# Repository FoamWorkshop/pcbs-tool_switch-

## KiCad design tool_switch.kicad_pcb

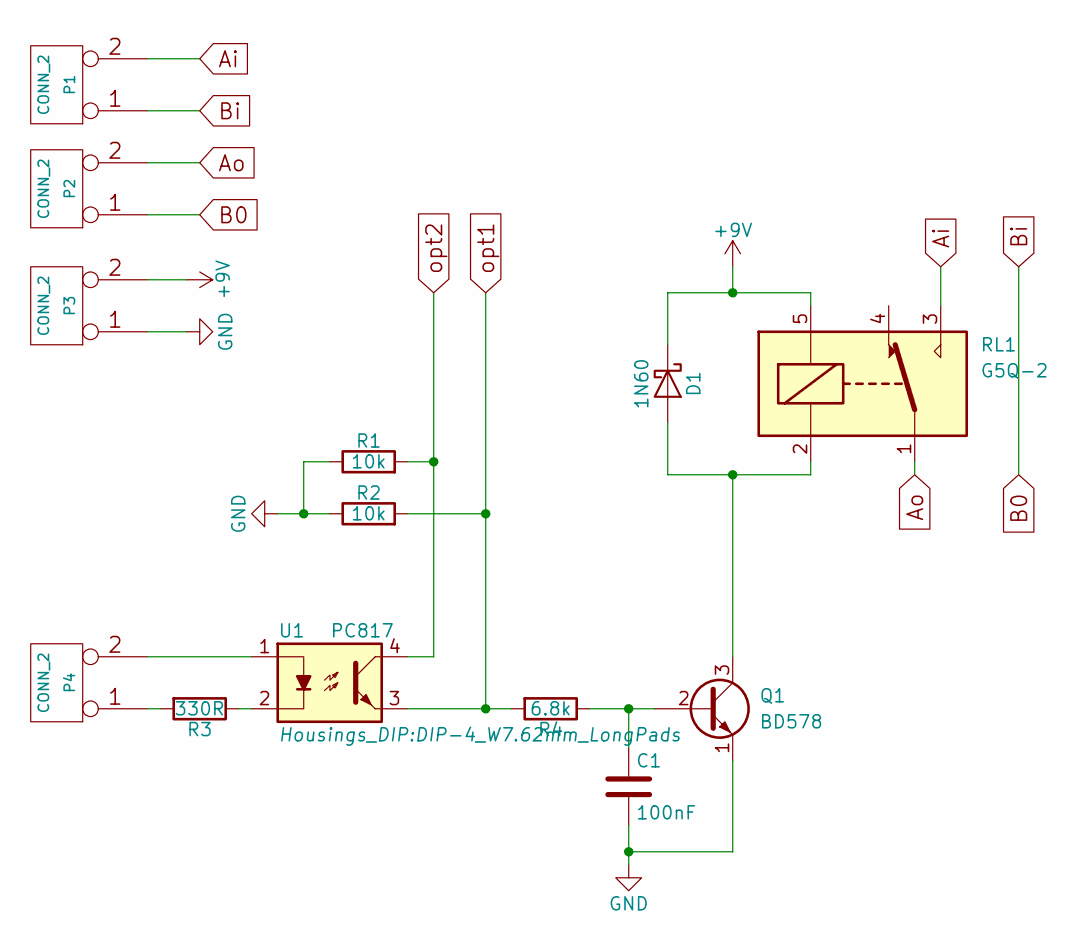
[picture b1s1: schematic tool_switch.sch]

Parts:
C1: 100nF; C_Disc_D3.0mm_W1.6mm_P2.50mm
D1: 1N60; D_A-405_P7.62mm_Horizontal
P1, P2, P3, P4: CONN_2; bornier2_V
Q1: BD578; TO-92_Inline_Narrow_Oval
R1, R2: 10k; R_Axial_DIN0204_L3.6mm_D1.6mm_P5.08mm_Horizontal
R3: 330R; R_Axial_DIN0204_L3.6mm_D1.6mm_P5.08mm_Horizontal
R4: 6.8k; R_Axial_DIN0204_L3.6mm_D1.6mm_P5.08mm_Horizontal
RL1: G5Q-2; Relay_SANYOU_SRD_Series_Form_C
U1: PC817; DIP-4_W7.62mm_LongPads

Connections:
+9V: D1.1 (K), P3.2, RL1.5; also elsewhere on the board
Ai: P1.2, RL1.3
Ao: P2.2, RL1.1
B0: P1.1, P2.1
GND: C1.2, P3.1, Q1.1 (E), R1.1, R2.1
unnamed: C1.1, Q1.2 (B), R4.1
unnamed: D1.2 (A), Q1.3 (C), RL1.2
unnamed: P4.1, R3.2
unnamed: P4.2, U1.1
unnamed: R3.1, U1.2
opt1: R2.2, R4.2, U1.3; also elsewhere on the board
opt2: R1.2, U1.4; also elsewhere on the board

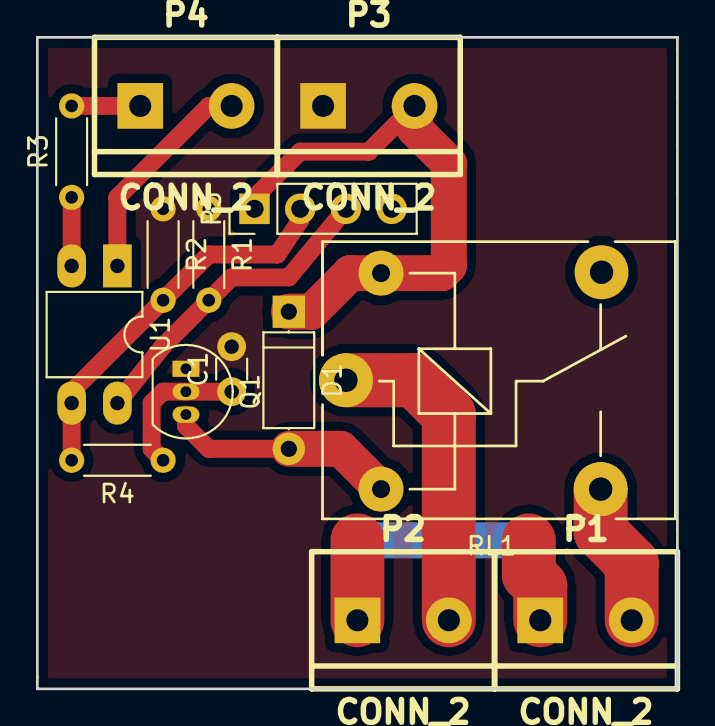
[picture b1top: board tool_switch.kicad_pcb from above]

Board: 2 copper layers, 35.6 x 36.2 mm, 14 parts (0 on the bottom side), 12 nets.

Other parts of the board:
P5: CONN_4; Pin_Header_Straight_1x04_Pitch2.54mm

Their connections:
+9V: P5.1; also elsewhere on the board
opt1: P5.2; also elsewhere on the board
opt2: P5.3; also elsewhere on the board

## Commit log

2017-01-24 version with a relay
2017-01-27 added pcb layout
